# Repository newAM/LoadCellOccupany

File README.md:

## Load Cell Occupancy Sensor

### What is it?
This project is a occupancy sensor that uses a load cell for couches and beds, transmitting data to my Home Assistant server via MQTT over Ethernet.

### Why?
Other bed occupancy sensors that I have used in my home automation setup trigger false negatives when rolling around at night.  I use bed occupancy to turn on my lights if I get up at night, and I wanted a faster, more accurate solution.

#### Why PoE?
Wireless home automation devices often make sense only when they are battery powered, if a power cable needs to be run to the device it can carry data too.  Designing a low power wireless device is far more complicated than designing a wired device and running an Ethernet cable.

## Overview
Load cells → HX711 (ADC) → ATMega328P (MCU) → W5100 (Ethernet) → MQTT Broker → Home Assistant

This sensor takes input from 4 load cells, each supporting one leg of a bed or couch.  The load cells are sampled with a ATMega328P (Arduino) using an HX711 load cell ADC.  These samples are then transmitted to an MQTT broker via the Wiznet W5100 (same as Arduino Ethernet shield).

## Project Contents
-  LoadCell_ArduinoCode - firmware for the ATMega328P
-  LoadCell_Case - 3D printable case designed in OpenSCAD
-  LoadCell_Holder - 3D printable holder for the load cells designed in OpenSCAD
-  LoadCell_HomeAssistant - example Home Assistant configuration
-  LoadCell_KiCAD - schematic and PCB

## Media

## Software Used
- [KiCad](http://kicad.org/)
- [Arduino IDE](https://www.arduino.cc/en/Main/Software)
- [OpenSCAD](http://www.openscad.org/)
- [Libre Office](https://www.libreoffice.org/)
- [Home Assistant](https://www.home-assistant.io/)

### Arduino Libraries used
- [Sparkfun HX711 Library](https://github.com/bogde/HX711)
- [Arduino MQTT Client](https://github.com/knolleary/pubsubclient)

## Forks
- [ESP8266 Load Cell](https://github.com/Skaronator/ESP8266-Load-Cell) - wireless edition

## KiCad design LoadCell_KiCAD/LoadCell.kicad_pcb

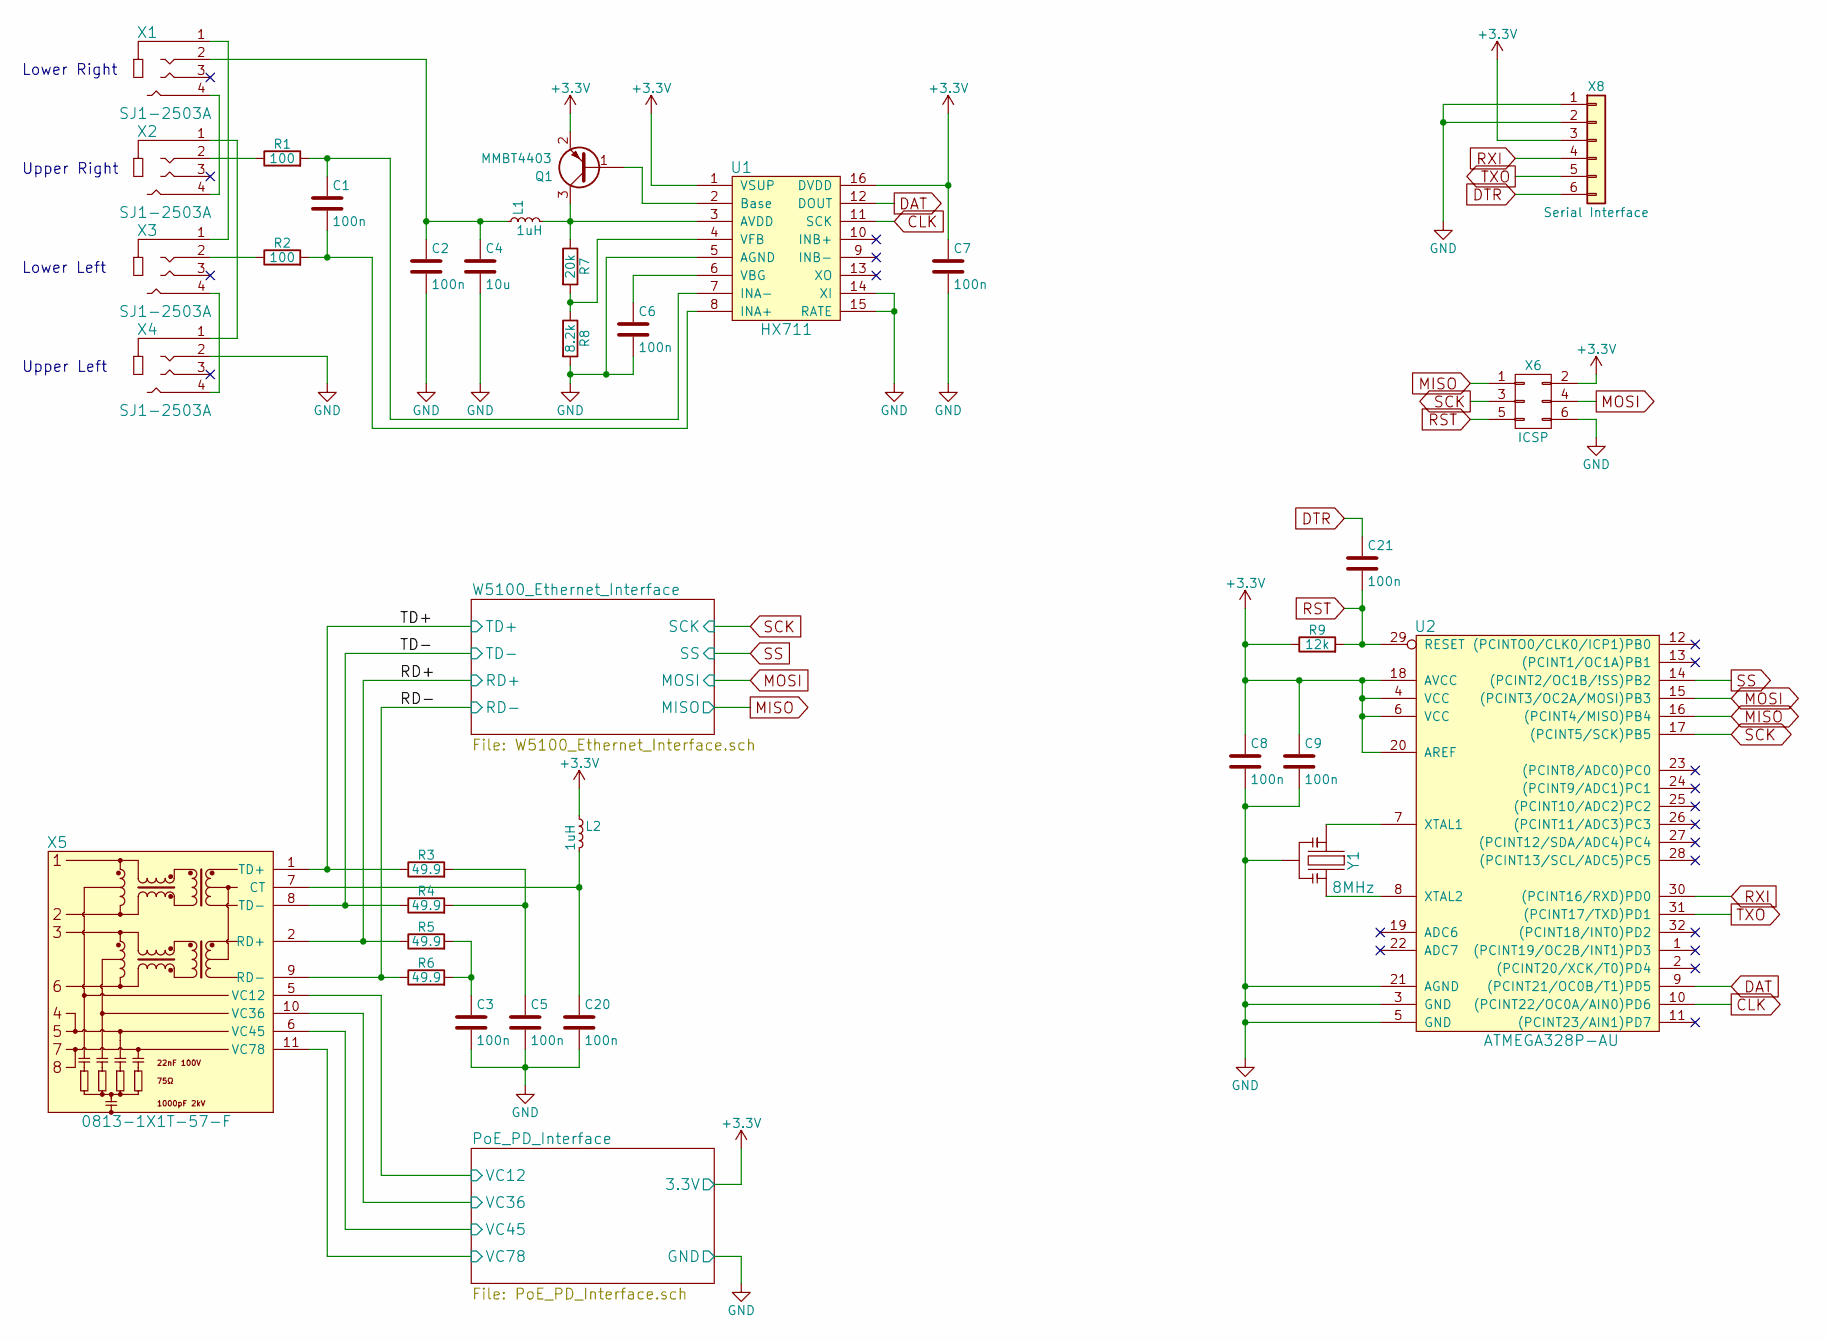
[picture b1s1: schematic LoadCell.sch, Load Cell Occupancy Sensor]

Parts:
C1, C2, C3, C5, C6, C7, C8, C9, C20, C21: 100n; C_0603; DigiKey Part Number 1276-1005-1-ND
C4: 10u; C_0805; DigiKey Part Number 1276-6456-1-ND
L1, L2: 1uH; C_0603; DigiKey Part Number 445-3163-1-ND
Q1: MMBT4403; SOT-23; DigiKey Part Number MMBT4403LT3GOSCT-ND
R1, R2: 100; R_0603; Tolerance 1%; DigiKey Part Number 311-100HRCT-ND
R3, R4, R5, R6: 49.9; R_0805; DigiKey Part Number RNCP0805FTD49R9CT-ND
R7: 20k; R_0603; Tolerance 1%; DigiKey Part Number 311-20.0KHRCT-ND
R8: 8.2k; R_0603; Tolerance 1%; DigiKey Part Number 311-8.20KHRCT-ND
R9: 12k; R_0603; Tolerance 1%; DigiKey Part Number 311-12.0KHRCT-ND
U1: HX711; SOIC-16_3.9x9.9mm_Pitch1.27mm
U2: ATMEGA328P-AU; TQFP-32_7x7mm_Pitch0.8mm; DigiKey Part Number ATMEGA328P-AU-ND
X1, X2, X3, X4: SJ1-2503A; DigiKey Part Number CP1-2503A-ND
X5: 0813-1X1T-57-F; 0813-1X1T-57-F_RJ45-Jack; DigiKey Part Number 507-1421-ND
X6: ICSP; Pin_Header_Straight_2x03_Pitch2.54mm
X8: Serial Interface; Pin_Header_Angled_1x06_Pitch2.54mm
Y1: 8MHz; CERALOCK_CSTCE_Resonator; DigiKey Part Number 490-1195-1-ND

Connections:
+3V3: C7.1, C8.1, C9.1, L2.1, Q1.2 (E), R9.1, U1.1 (VSUP), U1.16 (DVDD), U2.4 (VCC), U2.6 (VCC), U2.18 (AVCC), U2.20 (AREF), X6.2, X8.3; also elsewhere on the board
/PoE_PD_Interface/VC12: X5.5 (VC12); also elsewhere on the board
/PoE_PD_Interface/VC36: X5.10 (VC36); also elsewhere on the board
/PoE_PD_Interface/VC45: X5.6 (VC45); also elsewhere on the board
/PoE_PD_Interface/VC78: X5.11 (VC78); also elsewhere on the board
/RD+: R5.1, X5.2 (RD+); also elsewhere on the board
/RD-: R6.1, X5.9 (RD-); also elsewhere on the board
/TD+: R3.1, X5.1 (TD+); also elsewhere on the board
/TD-: R4.1, X5.8 (TD-); also elsewhere on the board
CLK: U1.11 (SCK), U2.10 ((PCINT22/OC0A/AIN0)PD6)
DAT: U1.12 (DOUT), U2.9 ((PCINT21/OC0B/T1)PD5)
DTR: C21.1, X8.6
GND: C2.2, C3.2, C4.2, C5.2, C6.2, C7.2, C8.2, C9.2, C20.2, R8.2, U1.5 (AGND), U1.14 (XI), U1.15 (RATE), U2.3 (GND), U2.5 (GND), U2.21 (AGND), X4.2, X6.6, X8.1, X8.2, Y1.2; also elsewhere on the board
MISO: U2.16 ((PCINT4/MISO)PB4), X6.1; also elsewhere on the board
MOSI: U2.15 ((PCINT3/OC2A/MOSI)PB3), X6.4; also elsewhere on the board
unnamed: C1.1, R1.2, U1.7 (INA-)
unnamed: C1.2, R2.2, U1.8 (INA+)
unnamed: C2.1, C4.1, L1.1, X1.2
unnamed: C3.1, R5.2, R6.2
unnamed: C5.1, R3.2, R4.2
unnamed: C6.1, U1.6 (VBG)
unnamed: C20.1, L2.2, X5.7 (CT)
unnamed: L1.2, Q1.3 (C), R7.1, U1.3 (AVDD)
unnamed: Q1.1 (B), U1.2 (Base)
unnamed: R1.1, X2.2
unnamed: R2.1, X3.2
unnamed: R7.2, R8.1, U1.4 (VFB)
unnamed: U2.7 (XTAL1), Y1.1
unnamed: U2.8 (XTAL2), Y1.3
unnamed: X1.1 (Case), X3.1 (Case)
unnamed: X1.4, X2.4
unnamed: X2.1 (Case), X4.1 (Case)
unnamed: X3.4, X4.4
RST: C21.2, R9.2, U2.29 (RESET), X6.5
RXI: U2.30 ((PCINT16/RXD)PD0), X8.4
SCK: U2.17 ((PCINT5/SCK)PB5), X6.3; also elsewhere on the board
SS: U2.14 ((PCINT2/OC1B/!SS)PB2); also elsewhere on the board
TXO: U2.31 ((PCINT17/TXD)PD1), X8.5

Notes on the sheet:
Upper Left
Lower Right
Upper Right
Lower Left

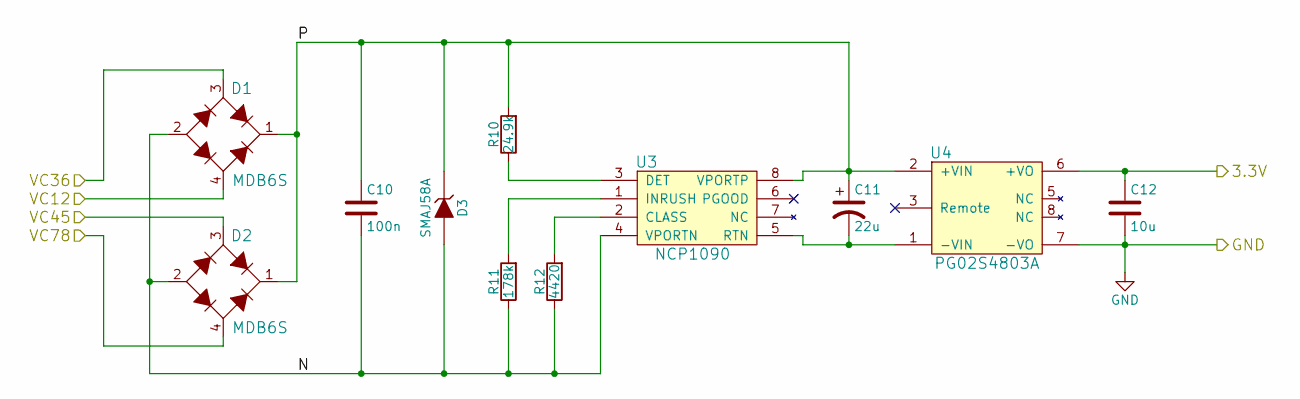
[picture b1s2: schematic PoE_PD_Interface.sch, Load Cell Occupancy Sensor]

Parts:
C10: 100n; C_0805; DigiKey Part Number 1276-6840-1-ND
C11: 22u; CP_Radial_D5.0mm_P2.00mm; DigiKey Part Number 493-12798-1-ND
C12: 10u; C_0805; DigiKey Part Number 1276-6456-1-ND
D1, D2: MDB6S; Micro-DIP-4; DigiKey Part Number MDB6SFSCT-ND
D3: SMAJ58A; D_SMA; DigiKey Part Number SMAJ58A-E3/61GICT-ND
R10: 24.9k; R_0603; DigiKey Part Number 311-24.9KHRCT-ND
R11: 178k; R_0603; DigiKey Part Number 311-178KHRCT-ND
R12: 4420; R_0603; DigiKey Part Number 311-4.42KHRCT-ND
U3: NCP1090; SOIC-8_3.9x4.9mm_Pitch1.27mm; DigiKey Part Number NCP1090DGOS-ND
U4: PG02S4803A; PG02S; DigiKey Part Number 941-1185-ND

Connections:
+3V3: C12.1, U4.6 (+VO); also elsewhere on the board
/PoE_PD_Interface/N: C10.2, D1.2 (-), D2.2 (-), D3.2 (A), R11.1, R12.1, U3.4 (VPORTN)
/PoE_PD_Interface/P: C10.1, C11.1, D1.1 (+), D2.1 (+), D3.1 (K), R10.2, U3.8 (VPORTP), U4.2 (+VIN)
/PoE_PD_Interface/VC12: D1.4 (AC2); also elsewhere on the board
/PoE_PD_Interface/VC36: D1.3 (AC1); also elsewhere on the board
/PoE_PD_Interface/VC45: D2.3 (AC1); also elsewhere on the board
/PoE_PD_Interface/VC78: D2.4 (AC2); also elsewhere on the board
GND: C12.2, U4.7 (-VO); also elsewhere on the board
unnamed: C11.2, U3.5 (RTN), U4.1 (-VIN)
unnamed: R10.1, U3.3 (DET)
unnamed: R11.2, U3.1 (INRUSH)
unnamed: R12.2, U3.2 (CLASS)

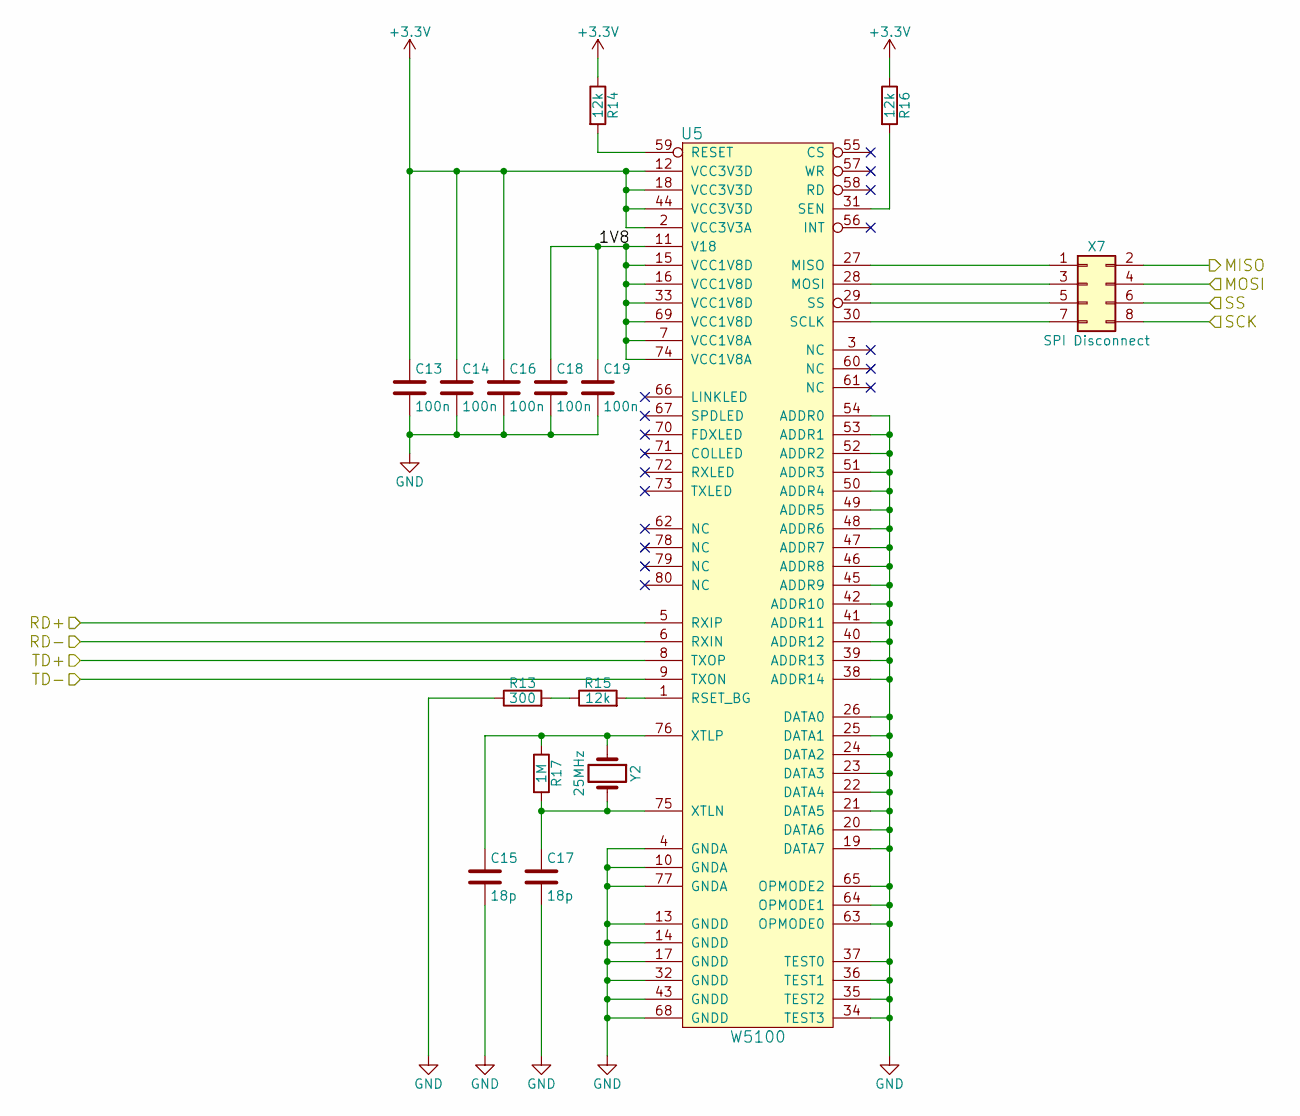
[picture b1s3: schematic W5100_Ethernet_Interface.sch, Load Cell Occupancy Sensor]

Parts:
C13, C14, C16, C18, C19: 100n; C_0603; DigiKey Part Number 1276-1005-1-ND
C15, C17: 18p; C_0603; DigiKey Part Number 1276-1089-1-ND
R13: 300; R_0603; Tolerance 1%; DigiKey Part Number 311-300HRCT-ND
R14, R15, R16: 12k; R_0603; Tolerance 1%; DigiKey Part Number 311-12.0KHRCT-ND
R17: 1M; R_0603; Tolerance 1%; DigiKey Part Number 311-1.00MHRCT-ND
U5: W5100; LQFP-80_10x10mm_Pitch0.4mm; DigiKey Part Number 1278-1002-ND
X7: SPI Disconnect; Pin_Header_Straight_2x04_Pitch2.54mm
Y2: 25MHz; Crystal_SMD_HC49-SD; DigiKey Part Number 535-10235-1-ND

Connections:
+3V3: C13.1, C14.1, C16.1, R14.1, R16.1, U5.2 (VCC3V3A), U5.12 (VCC3V3D), U5.18 (VCC3V3D), U5.44 (VCC3V3D); also elsewhere on the board
/RD+: U5.5 (RXIP); also elsewhere on the board
/RD-: U5.6 (RXIN); also elsewhere on the board
/TD+: U5.8 (TXOP); also elsewhere on the board
/TD-: U5.9 (TXON); also elsewhere on the board
/W5100_Ethernet_Interface/1V8: C18.1, C19.1, U5.7 (VCC1V8A), U5.11 (V18), U5.15 (VCC1V8D), U5.16 (VCC1V8D), U5.33 (VCC1V8D), U5.69 (VCC1V8D), U5.74 (VCC1V8A)
GND: C13.2, C14.2, C15.2, C16.2, C17.2, C18.2, C19.2, R13.1, U5.4 (GNDA), U5.10 (GNDA), U5.13 (GNDD), U5.14 (GNDD), U5.17 (GNDD), U5.19 (DATA7), U5.20 (DATA6), U5.21 (DATA5), U5.22 (DATA4), U5.23 (DATA3), U5.24 (DATA2), U5.25 (DATA1), U5.26 (DATA0), U5.32 (GNDD), U5.34 (TEST3), U5.35 (TEST2), U5.36 (TEST1), U5.37 (TEST0), U5.38 (ADDR14), U5.39 (ADDR13), U5.40 (ADDR12), U5.41 (ADDR11), U5.42 (ADDR10), U5.43 (GNDD), U5.45 (ADDR9), U5.46 (ADDR8), U5.47 (ADDR7), U5.48 (ADDR6), U5.49 (ADDR5), U5.50 (ADDR4), U5.51 (ADDR3), U5.52 (ADDR2), U5.53 (ADDR1), U5.54 (ADDR0), U5.63 (OPMODE0), U5.64 (OPMODE1), U5.65 (OPMODE2), U5.68 (GNDD), U5.77 (GNDA); also elsewhere on the board
MISO: X7.2; also elsewhere on the board
MOSI: X7.4; also elsewhere on the board
unnamed: C15.1, R17.1, U5.76 (XTLP), Y2.1
unnamed: C17.1, R17.2, U5.75 (XTLN), Y2.2
unnamed: R13.2, R15.1
unnamed: R14.2, U5.59 (RESET)
unnamed: R15.2, U5.1 (RSET_BG)
unnamed: R16.2, U5.31 (SEN)
unnamed: U5.27 (MISO), X7.1
unnamed: U5.28 (MOSI), X7.3
unnamed: U5.29 (SS), X7.5
unnamed: U5.30 (SCLK), X7.7
SCK: X7.8; also elsewhere on the board
SS: X7.6; also elsewhere on the board

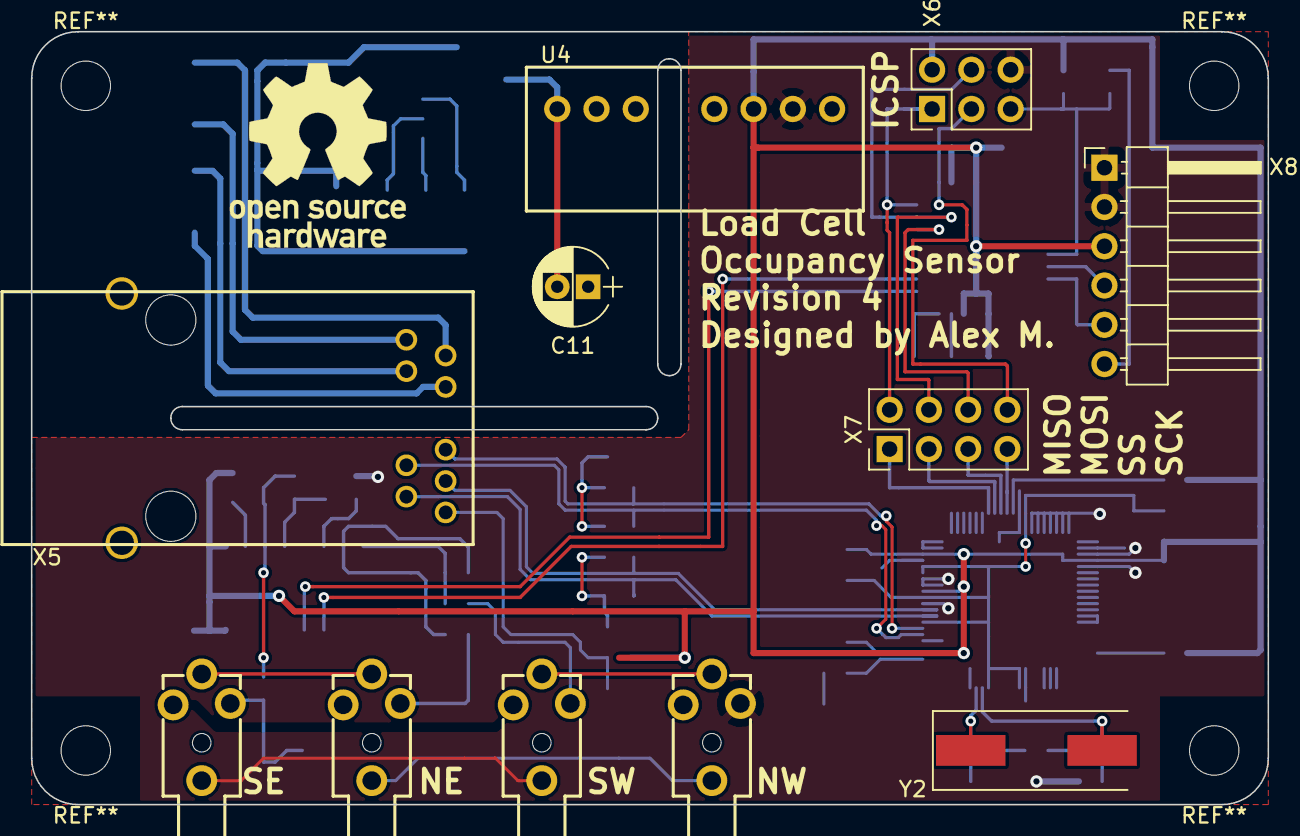
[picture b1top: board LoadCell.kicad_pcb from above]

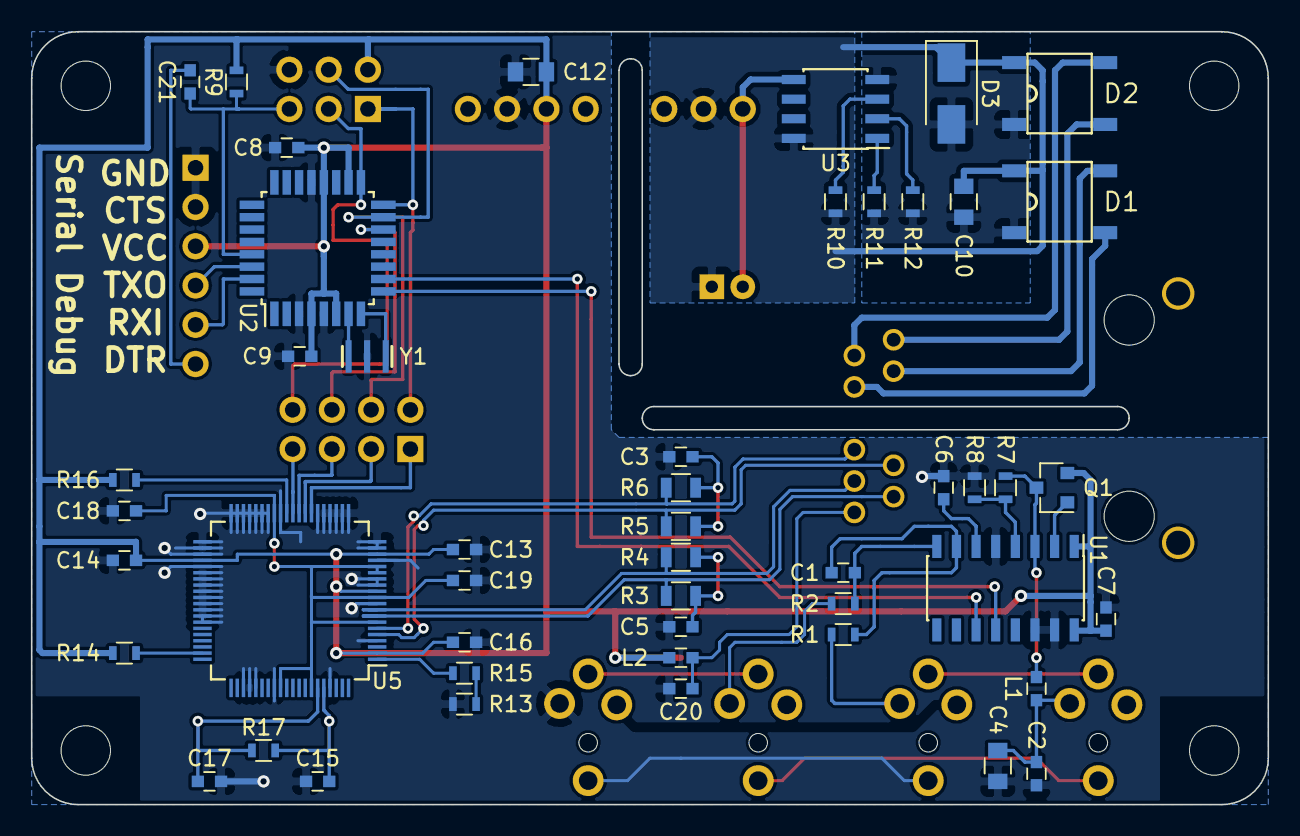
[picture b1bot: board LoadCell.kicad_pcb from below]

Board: 2 copper layers, 80.0 x 50.0 mm, 59 parts (48 on the bottom side), 55 nets.

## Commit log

2018-03-18 corrected lid dimensions after print
2018-03-18 updated readme to include the use of libre office for the bill of materials spreadsheet
2018-03-18 added mounting hardware to BoM
2018-04-29 added tare functionality and serial prints for debug
2018-04-29 added example home assistant configuration
2018-06-03 added pictures to readme. value is now only transmitted on change to reduce broker load
2018-10-07 fixed small typo in code
2019-03-21 Fix for issue #6
2019-05-29 Should use new hx711
2019-05-29 LoadCell ino file with wifi instead of ethernet
    Made some changes where the mqtt doesn't reconnect constantly. Only when active connection. For my sitiuation i measure the bed. Since if you move around at night it will do a lot of updates so i cha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
    Also copy pasted the over the air update from the other repo in your readme. Reason to adjust this one was that the other one crashed every now and then. I redid the wifi part and it seems to be soli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
    Last part is that if the value is a negative value i just reset it back to 0. Thi
2019-06-01 Remove HX711 versioning from README.
2021-11-08 Update README.md
    https://forum.kicad.info/t/warning-avoid-all-links-to-kicad-pcb-org-use-kicad-org/31521
